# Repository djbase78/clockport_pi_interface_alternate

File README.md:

# Alternative PCB for Niklas Ekström's "clockport pi interface"

This is a fork from Niklas Ekström where an alternate PCB layout has been made to enable an even smaller and more low-profile end product.
The fork contains PCB files in KiCAD 6.99 format, and an updated pin constraint file (.ucf) to accomodate for the new PCB.

|  |  |
|-------------|-------------|
|  |  |
|   |  |
|  |  |

## Details about how the interface works

For further details about this excellent project, please visit this forks origin site @ [niklasekstrom/clockport_pi_interface](https://github.com/niklasekstrom/clockport_pi_interface)
You will find a schematic PDF for this forked PCB in the Hardware folder.

## Bill of materials

| References                     | Value                                                | Footprint                       | Quantity |
|--------------------------------|------------------------------------------------------|---------------------------------|----------|
| C1, C2, C3, C4, C5, C6, C7, C8 | 0.1u                                                 | C_0603_1608Metric               | 8        |
| U1                             | XC9572XL-VQ64                                        | TQFP-64_10x10mm_P0.5mm          | 1        |
| IC2, IC3                       | SN74LVC573APWRE4<br>(alt: 74LVC573APW,118)           | SOP65P640X120-20N               | 2        |
| IC1                            | IS63WV1288DBLL-10TLI<br>(alt: IS61WV1288EEBLL-10TLI) | SOIC127P1176X120-32N            | 1        |
| J1                             | Raspberry Pi Zero 2W                                 | PinSocket_2x20_P2.54mm_Vertical | 1        |
| J2                             | Molex 87381-2218<br>2row, 11pos, 2mm grid            | PinSocket_2x11_P2.00mm_Vertical | 1        |

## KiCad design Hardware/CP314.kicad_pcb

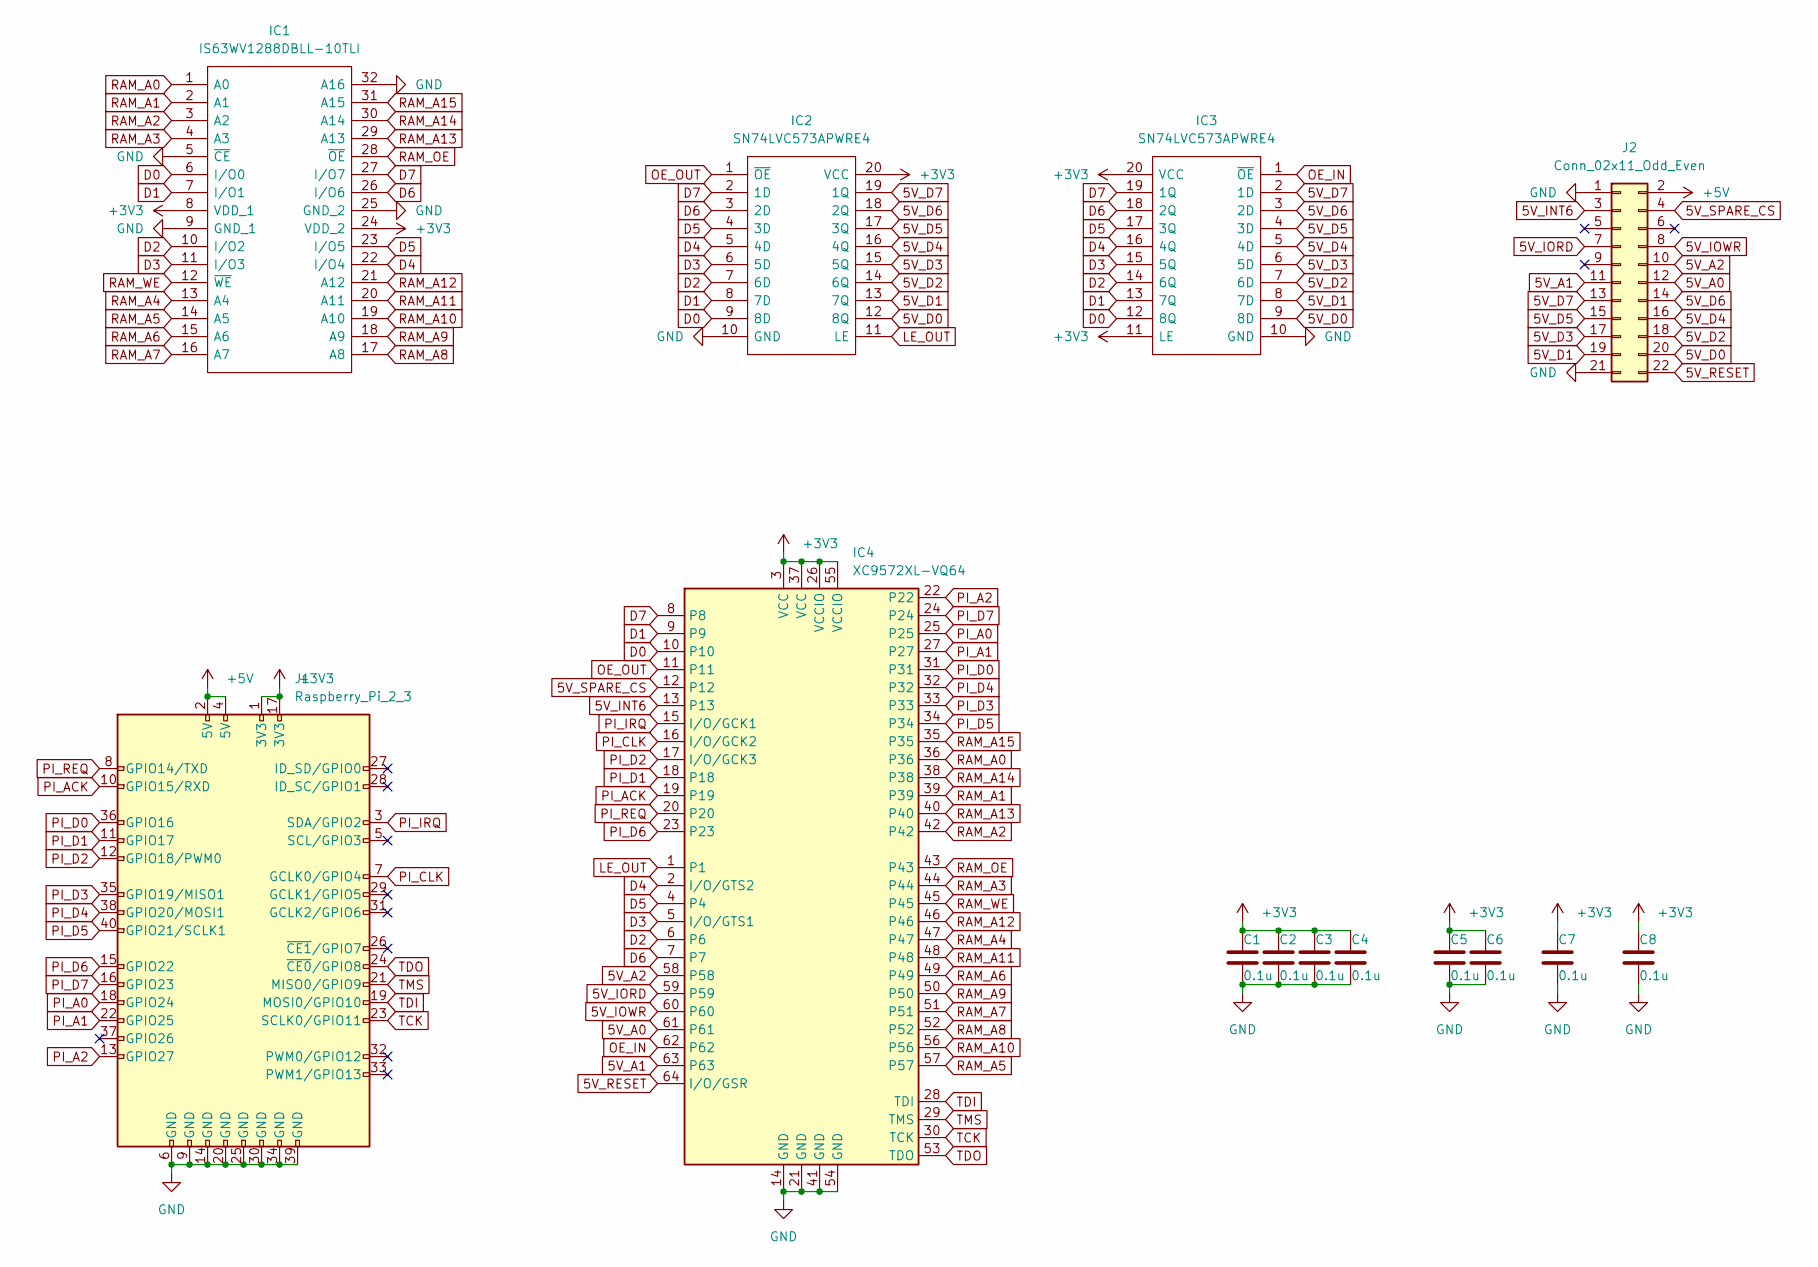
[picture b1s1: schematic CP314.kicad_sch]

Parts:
C1, C2, C3, C4, C5, C6, C7, C8: 0.1u; C_0603_1608Metric
IC1: IS63WV1288DBLL-10TLI; TSOP-II-32_21.0x10.2mm_P1.27mm; Mouser Part Number 870-63WV1288DB10TLI
IC2, IC3: SN74LVC573APWRE4; TSSOP-20_4.4x6.5mm_P0.65mm; Mouser Part Number 595-SN74LVC573APWRE4
IC4: XC9572XL-VQ64; TQFP-64_10x10mm_P0.5mm
J1: Raspberry_Pi_2_3; ADA3708_RPI-ZERO_NO_HOLES
J2: Conn_02x11_Odd_Even; PinSocket_2x11_P2.00mm_Vertical_SMD

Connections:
5V_A0: IC4.61, J2.12
5V_A1: IC4.63, J2.11
5V_A2: IC4.58, J2.10
5V_D0: IC2.12 (8Q), IC3.9 (8D), J2.20
5V_D1: IC2.13 (7Q), IC3.8 (7D), J2.19
5V_D2: IC2.14 (6Q), IC3.7 (6D), J2.18
5V_D3: IC2.15 (5Q), IC3.6 (5D), J2.17
5V_D4: IC2.16 (4Q), IC3.5 (4D), J2.16
5V_D5: IC2.17 (3Q), IC3.4 (3D), J2.15
5V_D6: IC2.18 (2Q), IC3.3 (2D), J2.14
5V_D7: IC2.19 (1Q), IC3.2 (1D), J2.13
5V_INT6: IC4.13, J2.3
5V_IORD: IC4.59, J2.7
5V_IOWR: IC4.60, J2.8
5V_RESET: IC4.64 (I/O/GSR), J2.22
5V_SPARE_CS: IC4.12, J2.4
+3V3: C1.1, C2.1, C3.1, C4.1, C5.1, C6.1, C7.1, C8.1, IC1.8 (VDD_1), IC1.24 (VDD_2), IC2.20 (VCC), IC3.11 (LE), IC3.20 (VCC), IC4.3 (VCC), IC4.26 (VCCIO), IC4.37 (VCC), IC4.55 (VCCIO), J1.1 (3V3), J1.17 (3V3)
+5V: J1.2 (5V), J1.4 (5V), J2.2
D0: IC1.6 (I/O0), IC2.9 (8D), IC3.12 (8Q), IC4.10
D1: IC1.7 (I/O1), IC2.8 (7D), IC3.13 (7Q), IC4.9
D2: IC1.10 (I/O2), IC2.7 (6D), IC3.14 (6Q), IC4.6
D3: IC1.11 (I/O3), IC2.6 (5D), IC3.15 (5Q), IC4.5 (I/O/GTS1)
D4: IC1.22 (I/O4), IC2.5 (4D), IC3.16 (4Q), IC4.2 (I/O/GTS2)
D5: IC1.23 (I/O5), IC2.4 (3D), IC3.17 (3Q), IC4.4
D6: IC1.26 (I/O6), IC2.3 (2D), IC3.18 (2Q), IC4.7
D7: IC1.27 (I/O7), IC2.2 (1D), IC3.19 (1Q), IC4.8
GND: C1.2, C2.2, C3.2, C4.2, C5.2, C6.2, C7.2, C8.2, IC1.5 (~CE), IC1.9 (GND_1), IC1.25 (GND_2), IC1.32 (A16), IC2.10 (GND), IC3.10 (GND), IC4.14 (GND), IC4.21 (GND), IC4.41 (GND), IC4.54 (GND), J1.6 (GND), J1.9 (GND), J1.14 (GND), J1.20 (GND), J1.25 (GND), J1.30 (GND), J1.34 (GND), J1.39 (GND), J2.1, J2.21
LE_OUT: IC2.11 (LE), IC4.1
OE_IN: IC3.1 (~OE), IC4.62
OE_OUT: IC2.1 (~OE), IC4.11
PI_A0: IC4.25, J1.18 (GPIO24)
PI_A1: IC4.27, J1.22 (GPIO25)
PI_A2: IC4.22, J1.13 (GPIO27)
PI_ACK: IC4.19, J1.10 (GPIO15/RXD)
PI_CLK: IC4.16 (I/O/GCK2), J1.7 (GCLK0/GPIO4)
PI_D0: IC4.31, J1.36 (GPIO16)
PI_D1: IC4.18, J1.11 (GPIO17)
PI_D2: IC4.17 (I/O/GCK3), J1.12 (GPIO18/PWM0)
PI_D3: IC4.33, J1.35 (GPIO19/MISO1)
PI_D4: IC4.32, J1.38 (GPIO20/MOSI1)
PI_D5: IC4.34, J1.40 (GPIO21/SCLK1)
PI_D6: IC4.23, J1.15 (GPIO22)
PI_D7: IC4.24, J1.16 (GPIO23)
PI_IRQ: IC4.15 (I/O/GCK1), J1.3 (SDA/GPIO2)
PI_REQ: IC4.20, J1.8 (GPIO14/TXD)
RAM_A0: IC1.1 (A0), IC4.36
RAM_A1: IC1.2 (A1), IC4.39
RAM_A2: IC1.3 (A2), IC4.42
RAM_A3: IC1.4 (A3), IC4.44
RAM_A4: IC1.13 (A4), IC4.47
RAM_A5: IC1.14 (A5), IC4.57
RAM_A6: IC1.15 (A6), IC4.49
RAM_A7: IC1.16 (A7), IC4.51
RAM_A8: IC1.17 (A8), IC4.52
RAM_A9: IC1.18 (A9), IC4.50
RAM_A10: IC1.19 (A10), IC4.56
RAM_A11: IC1.20 (A11), IC4.48
RAM_A12: IC1.21 (A12), IC4.46
RAM_A13: IC1.29 (A13), IC4.40
RAM_A14: IC1.30 (A14), IC4.38
RAM_A15: IC1.31 (A15), IC4.35
RAM_OE: IC1.28 (~OE), IC4.43
RAM_WE: IC1.12 (~WE), IC4.45
TCK: IC4.30 (TCK), J1.23 (SCLK0/GPIO11)
TDI: IC4.28 (TDI), J1.19 (MOSI0/GPIO10)
TDO: IC4.53 (TDO), J1.24 (~CE0/GPIO8)
TMS: IC4.29 (TMS), J1.21 (MISO0/GPIO9)

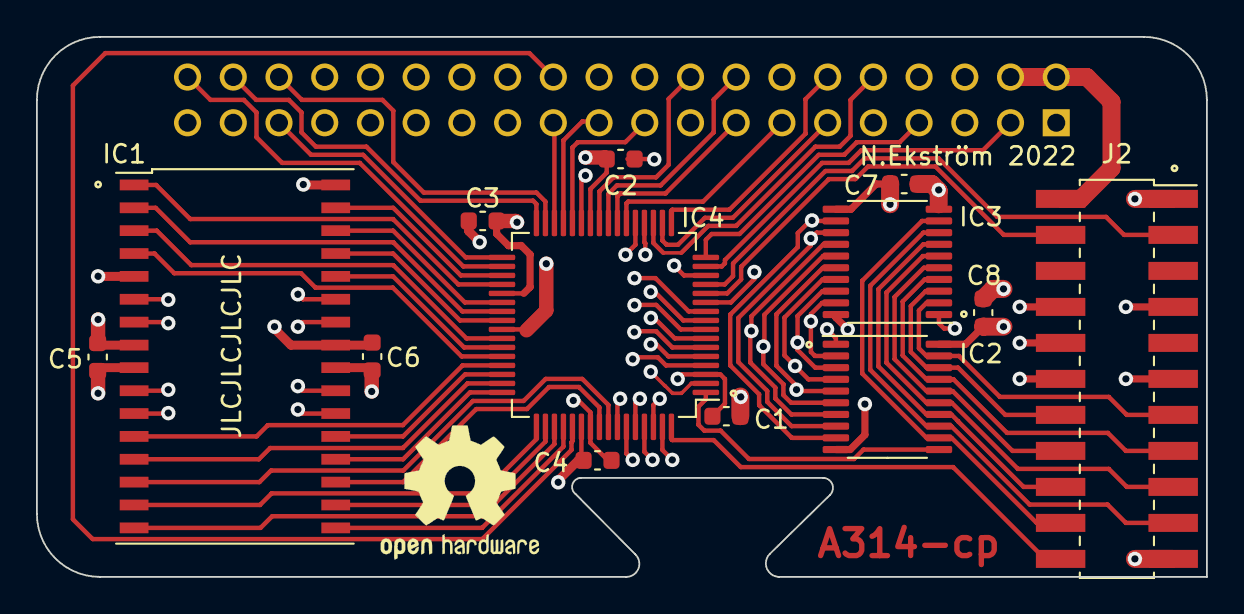
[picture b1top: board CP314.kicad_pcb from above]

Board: 4 copper layers, 65.0 x 30.0 mm, 14 parts (1 on the bottom side), 67 nets.

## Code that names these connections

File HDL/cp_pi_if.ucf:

#PACE: Start of Constraints generated by PACE

#PACE: Start of PACE I/O Pin Assignments
NET "CLK"  LOC = "P16"  ;
#NET "RESET_n"  LOC = "P64"  ;
NET "RTC_CS_n"  LOC = "P12"  ;
NET "IORD_n"  LOC = "P59"  ;
NET "IOWR_n"  LOC = "P60"  ;
NET "D<0>"  LOC = "P10"  ;
NET "D<1>"  LOC = "P9"  ;
NET "D<2>"  LOC = "P6"  ;
NET "D<3>"  LOC = "P5"  ;
NET "D<4>"  LOC = "P2"  ;
NET "D<5>"  LOC = "P4"  ;
NET "D<6>"  LOC = "P7"  ;
NET "D<7>"  LOC = "P8"  ;
NET "CP_A<0>"  LOC = "P61"  ;
NET "CP_A<1>"  LOC = "P63"  ;
#NET "CP_A<2>"  LOC = "P58"  ;
NET "INT6_n"  LOC = "P13"  ;
NET "LE_OUT"  LOC = "P1"  ;
NET "OE_OUT_n"  LOC = "P11"  ;
NET "OE_IN_n"  LOC = "P62"  ;
NET "PI_REQ"  LOC = "P20"  ;
NET "PI_ACK"  LOC = "P19"  ;
NET "PI_A<0>"  LOC = "P25"  ;
NET "PI_A<1>"  LOC = "P27"  ;
NET "PI_WR"  LOC = "P22"  ;
NET "PI_D<0>"  LOC = "P31"  ;
NET "PI_D<1>"  LOC = "P18"  ;
NET "PI_D<2>"  LOC = "P17"  ;
NET "PI_D<3>"  LOC = "P33"  ;
NET "PI_D<4>"  LOC = "P32"  ;
NET "PI_D<5>"  LOC = "P34"  ;
NET "PI_D<6>"  LOC = "P23"  ;
NET "PI_D<7>"  LOC = "P24"  ;
NET "PI_IRQ"  LOC = "P15"  ;
NET "RAM_A<0>"  LOC = "P36"  ;
NET "RAM_A<1>"  LOC = "P39"  ;
NET "RAM_A<2>"  LOC = "P42"  ;
NET "RAM_A<3>"  LOC = "P44"  ;
NET "RAM_A<4>"  LOC = "P47"  ;
NET "RAM_A<5>"  LOC = "P57"  ;
NET "RAM_A<6>"  LOC = "P49"  ;
NET "RAM_A<7>"  LOC = "P51"  ;
NET "RAM_A<8>"  LOC = "P52"  ;
NET "RAM_A<9>"  LOC = "P50"  ;
NET "RAM_A<10>"  LOC = "P56"  ;
NET "RAM_A<11>"  LOC = "P48"  ;
NET "RAM_A<12>"  LOC = "P46"  ;
NET "RAM_A<13>"  LOC = "P40"  ;
NET "RAM_A<14>"  LOC = "P38"  ;
NET "RAM_A<15>"  LOC = "P35"  ;
NET "RAM_OE_n"  LOC = "P43"  ;
NET "RAM_WE_n"  LOC = "P45"  ;

#PACE: Start of PACE Area Constraints

#PACE: Start of PACE Prohibit Constraints

#PACE: End of Constraints generated by PACE
